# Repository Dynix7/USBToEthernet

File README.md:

# USBToEthernet
This is a design for USB to Ethernet Adapter that (obviously) allows you to use ethernet through a USB port.

# Why I Made It
I made this PCB because I was getting into setting up some sort of homeserver using my old laptop. However, my laptop doesn't have an ethernet port and while I could use WIFI, it wouldn't be optimal for network speed.

# Picture

# BOM

|Name                      |Purpose                       |Quantity|Total Cost (USD)|Link                                                                                                                                                                             |Distributor|
|--------------------------|------------------------------|--------|----------------|---------------------------------------------------------------------------------------------------------------------------------------------------------------------------------|-----------|
|10k Resistor              |Resistor                      |        |0.06            |https://www.lcsc.com/product-detail/C2906861.html|LCSC       |
|8.06k Resistor            |Resistor                      |        |0.01            |https://www.lcsc.com/product-detail/C2960789.html|LCSC       |
|12k Resistor              |Resistor                      |        |0.06            |https://www.lcsc.com/product-detail/C2909316.html|LCSC       |
|1k Resistor               |Resistor                      |        |0.06            |https://www.lcsc.com/product-detail/C2906864.html|LCSC       |
|49.9 Capcitor             |Capacitor                     |        |0.06            |https://www.lcsc.com/product-detail/C2933103.html|LCSC       |
|24pF Capacitor            |Capacitor                     |        |0.12            |https://www.lcsc.com/product-detail/C281755.html |LCSC       |
|100nF Capacitor           |Decoupling Capacitor          |        |0.10            |https://www.lcsc.com/product-detail/C60474.html  |LCSC       |
|10uF Capacitor            |Capacitor                     |        |0.18            |https://www.lcsc.com/product-detail/C14445.html  |LCSC       |
|1uF Capacitor             |Capacitor                     |        |0.23            |https://www.lcsc.com/product-detail/C14445.html  |LCSC       |
|22nF Capacitor            |Capacitor                     |        |0.20            |https://www.lcsc.com/product-detail/C1532.html   |LCSC       |
|120 Ohm Ferrite Bead      |Power Filtering               |5       |0.90            |https://www.digikey.com/short/c9nm3n45                                                                                                                                           |Digikey    |
|USBLC6-2SC6               |Power Protection              |1       |0.36            |https://www.digikey.com/short/m59b7dzr                                                                                                                                           |Digikey    |
|NCP1117 Voltage Regulator |Voltage Regulator             |1       |0.38            |https://www.digikey.com/short/pvbpmpzr                                                                                                                                           |Digikey    |
|USB Plug                  |For Plugging Into Computer    |1       |1.35            |https://www.digikey.com/short/75mfb4tp                                                                                                                                           |Digikey    |
|PTS645S Push Button       |Reset Button                  |1       |0.36            |https://www.digikey.com/short/q00wnt84                                                                                                                                           |Digikey    |
|L836-1J1T-43 Ehternet Jack|Ethernet Jack                 |1       |6.53            |https://www.digikey.com/short/7bz57dt5                                                                                                                                           |Digikey    |
|AMS117 1.2V               |Voltage Regulator for LAN7500 |1       |0.10            |https://www.digikey.com/short/jqn99nv8                                                                                                                                           |Digikey    |
|93LC56AT-I/OT             |Storage                       |1       |0.32            |https://www.digikey.com/short/z01d9wp0                                                                                                                                           |Digikey    |
|TSX-3225 25Mhz Crystal    |Crystal Oscillator for LAN7500|1       |0.38            |https://www.digikey.com/short/hw0jtcmv                                                                                                                                           |Digikey    |
|LAN7500-ABZJ              |USB to Ethernet Chip          |1       |7.00            |https://www.digikey.com/short/8pjfdmbz                                                                                                                                           |Digikey    |
|Stencil                   |Stencil for Manually Assembly |1       |7.11            |                                                                                                                                                                                 |JLCPCB     |
|PCB                       |PCB for Build                 |5       |5.20            |                                                                                                                                                                                 |JLCPCB     |

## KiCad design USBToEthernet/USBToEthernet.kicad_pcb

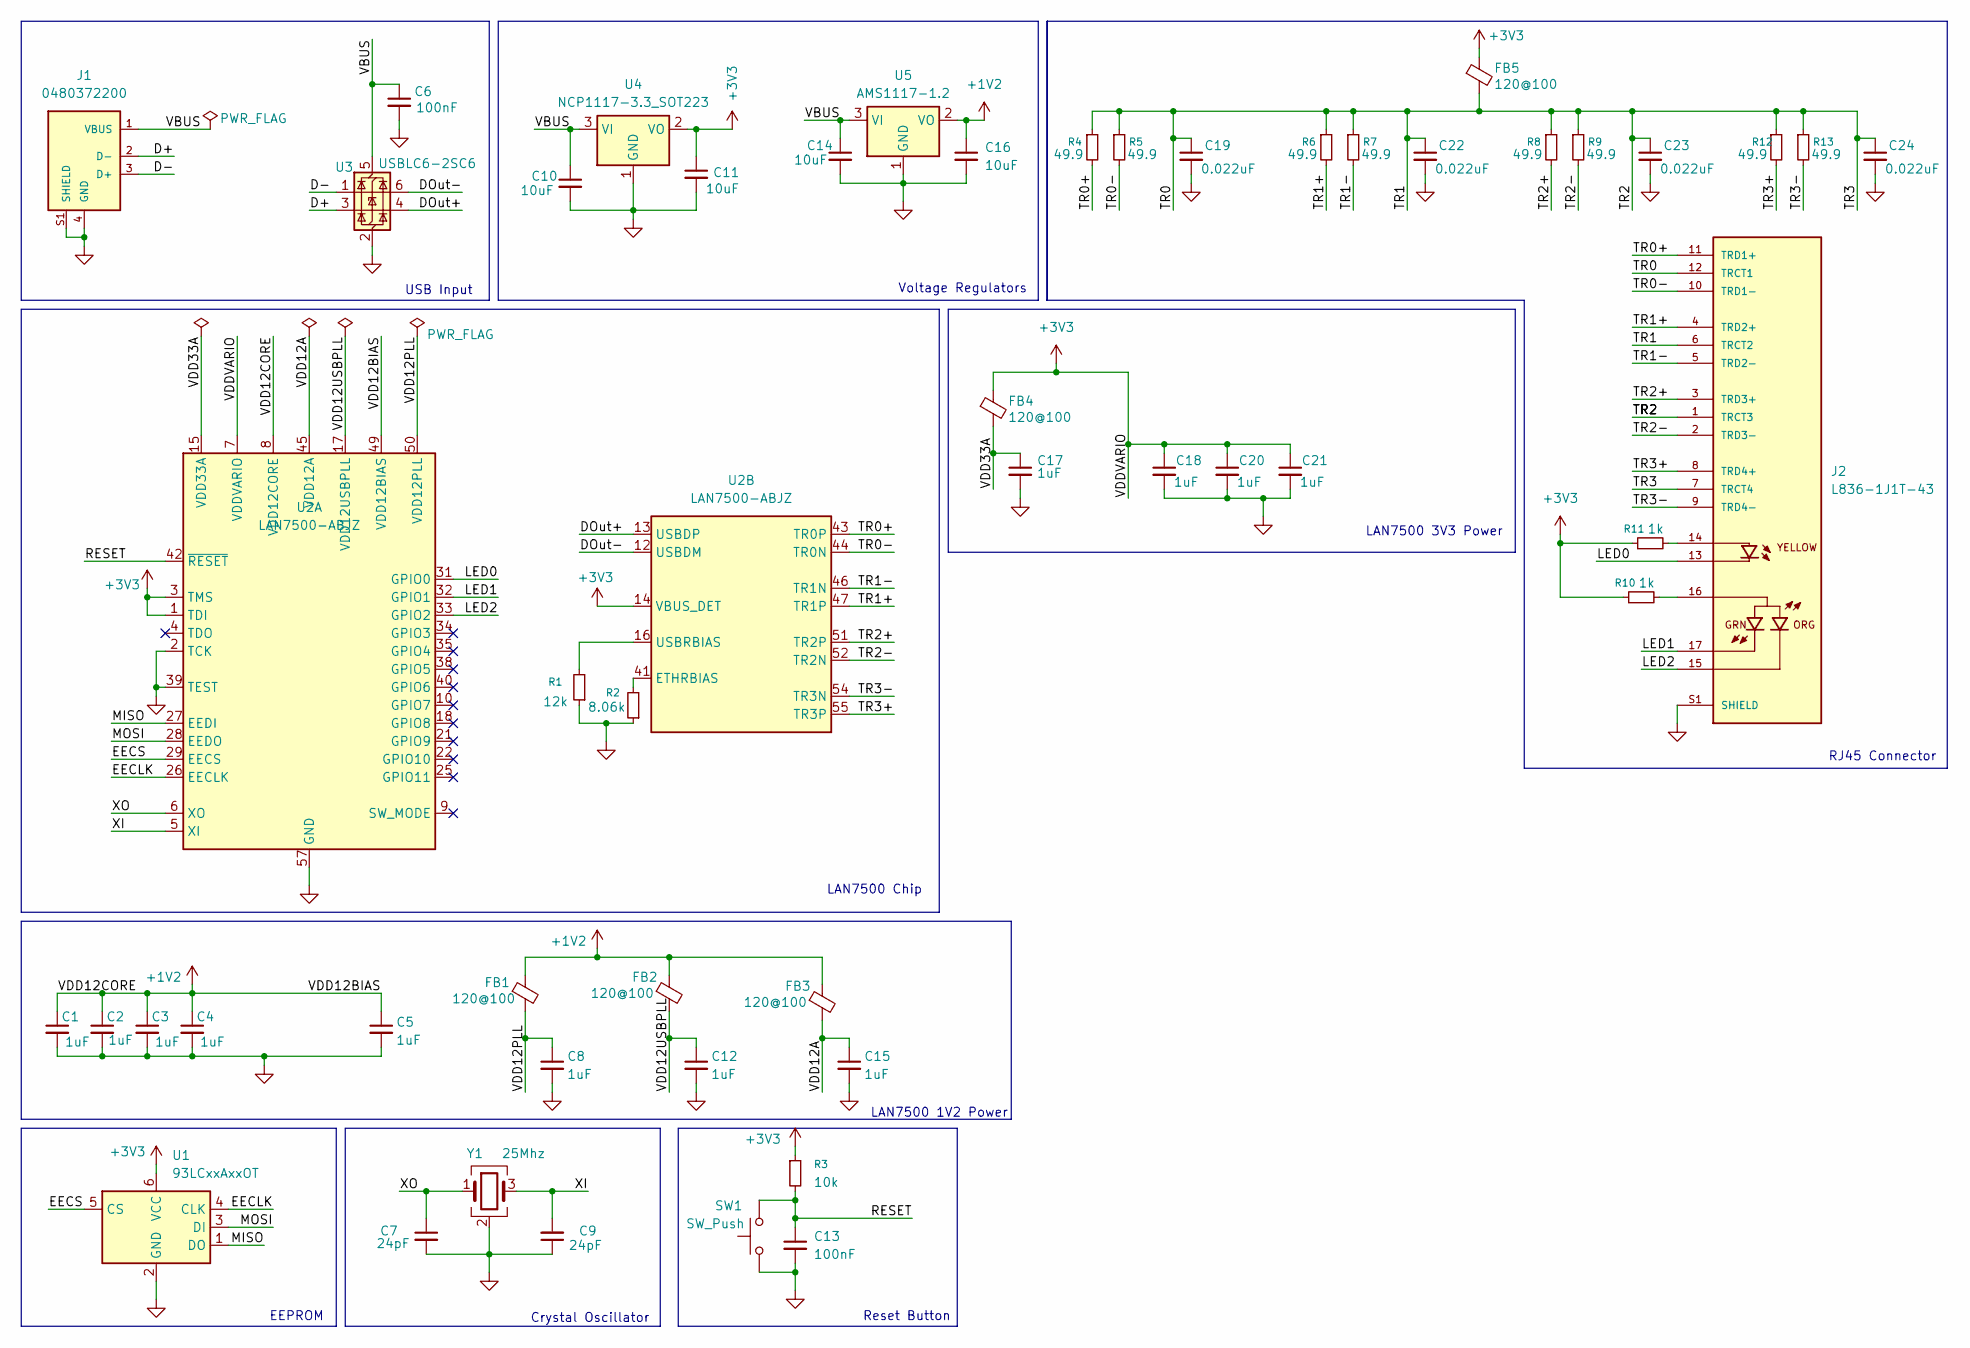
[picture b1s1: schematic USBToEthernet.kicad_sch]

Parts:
C1, C2, C3, C4, C12, C15, C17, C18, C20, C21: 1uF; C_0402_1005Metric
C5, C8: 1uF; C_0402_1005Metric_Pad0.74x0.62mm_HandSolder
C6, C13: 100nF; C_0402_1005Metric
C7, C9: 24pF; C_0402_1005Metric
C10, C11, C14, C16: 10uF; C_0402_1005Metric
C19, C22, C23, C24: 0.022uF; C_0402_1005Metric
FB1, FB2: 120@100; L_0402_1005Metric_Pad0.77x0.64mm_HandSolder
FB3, FB4, FB5: 120@100; L_0402_1005Metric
J1: 0480372200; MOLEX_0480372200
J2: L836-1J1T-43; BEL_L836-1J1T-43; PARTREV B; DigiKey_Part_Number 5923-L836-1J1T-43-ND
R1: 12k; R_0402_1005Metric_Pad0.72x0.64mm_HandSolder
R2: 8.06k; R_0402_1005Metric
R3: 10k; R_0402_1005Metric
R4, R5, R6, R7, R8, R9, R12, R13: 49.9; R_0402_1005Metric
R10, R11: 1k; R_0402_1005Metric
SW1: SW_Push; SW_SPST_PTS645Sx43SMTR92
U1: 93LCxxAxxOT; SOT-23-6
U2: LAN7500-ABJZ; QFN-56-1EP_8x8mm_P0.5mm_EP5.9x5.9mm
U3: USBLC6-2SC6; SOT-23-6
U4: NCP1117-3.3_SOT223; SOT-223-3_TabPin2
U5: AMS1117-1.2; SOT-223-3_TabPin2
Y1: 25Mhz; Crystal_SMD_SeikoEpson_FA238V-4Pin_3.2x2.5mm

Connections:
+1V2: C1.1, C2.1, C3.1, C4.1, C5.1, C16.1, FB1.1, FB2.1, FB3.1, U2.8 (VDD12CORE), U2.11 (VDD12CORE), U2.20 (VDD12CORE), U2.23 (VDD12CORE), U2.30 (VDD12CORE), U2.36 (VDD12CORE), U2.49 (VDD12BIAS), U5.2 (VO); also elsewhere on the board
+3V3: C11.1, C18.1, C20.1, C21.1, FB4.1, FB5.1, R3.1, R10.1, R11.1, U1.6 (VCC), U2.1 (TDI), U2.3 (TMS), U2.7 (VDDVARIO), U2.14 (VBUS_DET), U2.19 (VDDVARIO), U2.24 (VDDVARIO), U2.37 (VDDVARIO), U4.2 (VO)
/D+: J1.2 (D-), U3.3 (I/O2)
/D-: J1.3 (D+), U3.1 (I/O1)
/DOut+: U2.13 (USBDP), U3.4 (I/O2)
/DOut-: U2.12 (USBDM), U3.6 (I/O1)
/EECLK: U1.4 (CLK), U2.26 (EECLK)
/EECS: U1.5 (CS), U2.29 (EECS)
/LED0: J2.13, U2.31 (GPIO0)
/LED1: J2.17, U2.32 (GPIO1)
/LED2: J2.15, U2.33 (GPIO2)
/MISO: U1.1 (DO), U2.27 (EEDI)
/MOSI: U1.3 (DI), U2.28 (EEDO)
/RESET: C13.1, R3.2, SW1.2, U2.42 (~RESET)
/TR0: C19.1, C22.1, C23.1, C24.1, FB5.2, J2.1 (TRCT3), J2.6 (TRCT2), J2.7 (TRCT4), J2.12 (TRCT1), R4.1, R5.1, R6.1, R7.1, R8.1, R9.1, R12.1, R13.1
/TR0+: J2.11 (TRD1+), R4.2, U2.43 (TR0P)
/TR0-: J2.10 (TRD1-), R5.2, U2.44 (TR0N)
/TR1+: J2.4 (TRD2+), R6.2, U2.47 (TR1P)
/TR1-: J2.5 (TRD2-), R7.2, U2.46 (TR1N)
/TR2+: J2.3 (TRD3+), R8.2, U2.51 (TR2P)
/TR2-: J2.2 (TRD3-), R9.2, U2.52 (TR2N)
/TR3+: J2.8 (TRD4+), R12.2, U2.55 (TR3P)
/TR3-: J2.9 (TRD4-), R13.2, U2.54 (TR3N)
/VBUS: C6.1, C10.1, C14.1, J1.1 (VBUS), U3.5 (VBUS), U4.3 (VI), U5.3 (VI)
/VDD12A: C15.1, FB3.2, U2.45 (VDD12A), U2.48 (VDD12A), U2.53 (VDD12A), U2.56 (VDD12A)
/VDD12PLL: C8.1, FB1.2, U2.50 (VDD12PLL)
/VDD12USBPLL: C12.1, FB2.2, U2.17 (VDD12USBPLL)
/VDD33A: C17.1, FB4.2, U2.15 (VDD33A)
/XI: C9.2, U2.5 (XI), Y1.3
/XO: C7.1, U2.6 (XO), Y1.1
GND: C1.2, C2.2, C3.2, C4.2, C5.2, C6.2, C7.2, C8.2, C9.1, C10.2, C11.2, C12.2, C13.2, C14.2, C15.2, C16.2, C17.2, C18.2, C19.2, C20.2, C21.2, C22.2, C23.2, C24.2, J1.4 (GND), J1.S1 (SHIELD), J2.S1 (SHIELD), J2.S2 (SHIELD), R1.1, R2.1, SW1.1, U1.2 (GND), U2.2 (TCK), U2.39 (TEST), U2.57 (GND), U3.2 (GND), U4.1 (GND), U5.1 (GND), Y1.2 (G), Y1.4 (G); also elsewhere on the board
unnamed: J2.14, R11.2
unnamed: J2.16, R10.2
unnamed: R2.2, U2.41 (ETHRBIAS)
unnamed: R1.2, U2.16 (USBRBIAS)

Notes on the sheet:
LAN7500 3V3 Power
USB Input
EEPROM
LAN7500 1V2 Power
Crystal Oscillator
Reset Button
LAN7500 Chip
RJ45 Connector
Voltage Regulators

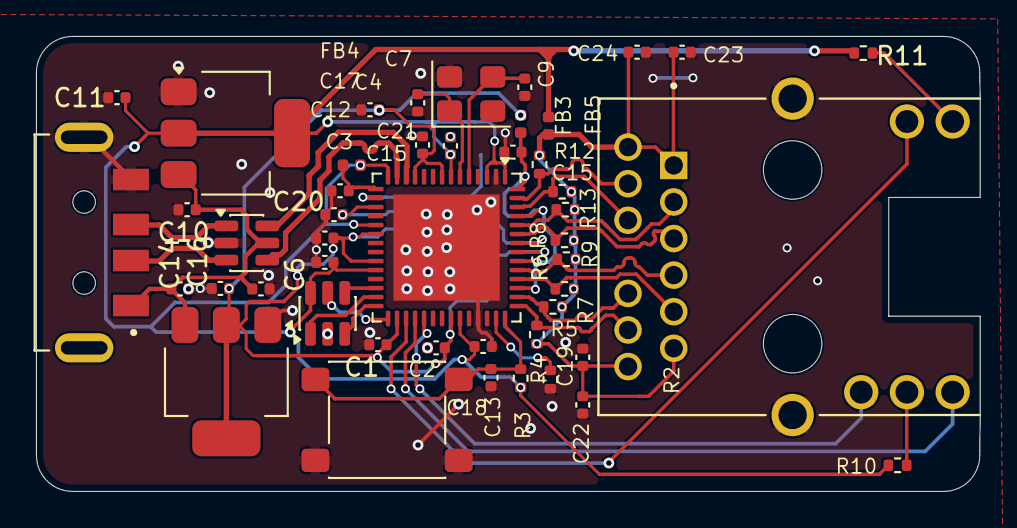
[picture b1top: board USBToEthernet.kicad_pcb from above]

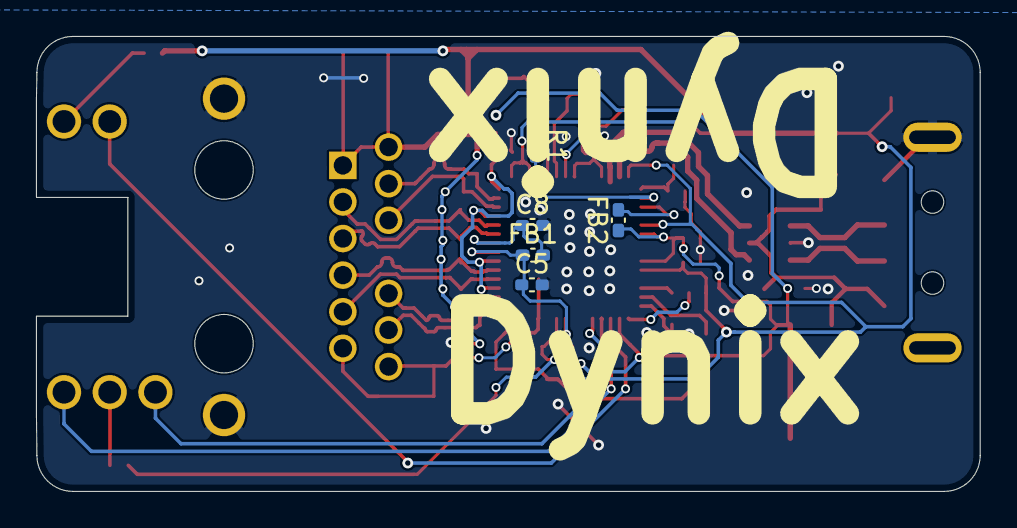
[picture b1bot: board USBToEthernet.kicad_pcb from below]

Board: 4 copper layers, 52.4 x 25.3 mm, 52 parts (5 on the bottom side), 35 nets.

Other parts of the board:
C15#2: 1uF; C_0402_1005Metric

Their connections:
+1V2: C15#2.1; also elsewhere on the board
GND: C15#2.2; also elsewhere on the board

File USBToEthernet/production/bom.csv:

Designator,Footprint,Quantity,Value,LCSC Part #
"C1, C12, C15_2, C15, C17, C18, C2, C20, C21, C3, C4, C5, C8",0402,13,1uF,
"C10, C11, C14, C16",0402,4,10uF,
"C13, C6",0402,2,100nF,
"C19, C22, C23, C24",0402,4,0.022uF,
"C7, C9",0402,2,24pF,
"FB1, FB2, FB3, FB4, FB5",0402,5,120@100,
J1,MOLEX_0480372200,1,0480372200,
J2,BEL_L836-1J1T-43,1,L836-1J1T-43,
R1,0402,1,12k,
"R10, R11",0402,2,1k,
"R12, R13, R4, R5, R6, R7, R8, R9",0402,8,49.9,
R2,0402,1,8.06k,
R3,0402,1,10k,
SW1,SW_SPST_PTS645Sx43SMTR92,1,SW_Push,
U1,SOT-23-6,1,93LCxxAxxOT,
U2,QFN-56-1EP_8x8mm_P0.5mm_EP5.9x5.9mm,1,LAN7500-ABJZ,
U3,SOT-23-6,1,USBLC6-2SC6,
U4,SOT-223-3_TabPin2,1,NCP1117-3.3_SOT223,
U5,SOT-223-3_TabPin2,1,AMS1117-1.2,
Y1,Crystal_SMD_SeikoEpson_FA238V-4Pin_3.2x2.5mm,1,25Mhz,

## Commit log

2026-02-18 Added parts
2026-02-18 Added library for RJ45
2026-02-19 Finished wiring RJ45 and most of LAN7500
2026-02-19 Finished schematic
2026-02-20 misc. changes
2026-02-20 Add external load capacitors for oscillator
2026-02-20 Add footprints for the oscillator load capacitors
2026-02-20 capacitor footprint
2026-02-20 Most placements I think done
2026-02-21 Fried ahh PCB layout and routing
2026-02-21 Will redo layout
2026-02-22 Revamped the PCB
2026-02-24 Change Via hole size
2026-03-07 Reroute again
2026-03-07 Reroute and other changes
2026-04-02 update repo fr
2026-04-19 update ibom and production
2026-04-20 Images
2026-05-09 Added more space between capacitors
